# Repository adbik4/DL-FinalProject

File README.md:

# Dokumentacja projektu
## Schemat blokowy

## Schemat ideowy

## Design PCB

## Podgląd 3D

### Blok mikrokontrolera (ATmega328PB)
*Obliczanie wartości pojemności C1 i C2 potrzebnych do zewnętrznego oscylatora MCU:*    

Wybraliśmy CY16BPS ponieważ jego parametry należą do najpopularniejszych do użycia w projektach z tym MCU.    
Oto jego najważniejsze parametry:   
- F_XTAL = 16 MHz
- C_load = 20 pF
- ESR = 50 ohm

Dla uproszczenia obliczeń, niech C1 = C2.    
Korzystając ze wzoru z dokumentacji ATmega,   
**C = 2 * C_L + C_S**  
gdzie     
C_L - Pojemnosć obciążenia kryształu,   
C_S - Pojemność pasożytnicza płytki PCB, niech wynosi 2 pF
    
Dla naszego kryształu C_L wynosi 20 pF    
**Stąd wynika, że C powinno mieć wartość około 42 pF.**

### Diody LED do sygnalizacji
*Obliczanie wartości rezystancji R1, R2 i R3 potrzebnych do uregulowania pracy diód:*     
    
Napięcie zasilania: 3.3V
Kolor diód LED: zielony co oznacza spadek napięcia około 2.2V   
Chcemy ustalić bezpieczny punkt pracy, powiedzmy 10mA    
Z prawa ohma: R = U / I = (3.3 - 2.2) / 10 mA = **110 ohm**

### Rezystancja podciągająca dla linii I2C
Wartość rezystancji podciągającej dla I2C jest wymianą pomiędzy możliwą prędkością wymiany danych a zużyciem energii.     

Zbyt mała wartość może uniemożliwić pinowi układu scalonego z którym się komunikujemy zwarcie linii z masą. Zalezy ona więc od najniższego napięcia jaka może być odczytana przez dany ukł. (U_OL) oraz prądu jaki jest on w stanie wytrzymać (I_OL).     

**R_min = (V_CC - U_OLmax) / I_OL**     

Zbyt duża zaś, przy dużych prędkościach może nie nadążyć z naładowaniem pojemności magistrali (C_m) przed nadejściem kolejnego stanu niskiego. W związku z tym, zależy ona od czasu narastania zboczy.     

**R_max = t_r / (0.8473 * C_m)**     
*Wartość 0.8473 = -ln(0.3) wynika z czasu ładowania pojemności od  30% - 70%*     

Przy naszych małych prędkościach komunikacji oraz z pojedynczym urządzeniem na magistrali, przyjmiemy standardową wartość **4.7kΩ.**

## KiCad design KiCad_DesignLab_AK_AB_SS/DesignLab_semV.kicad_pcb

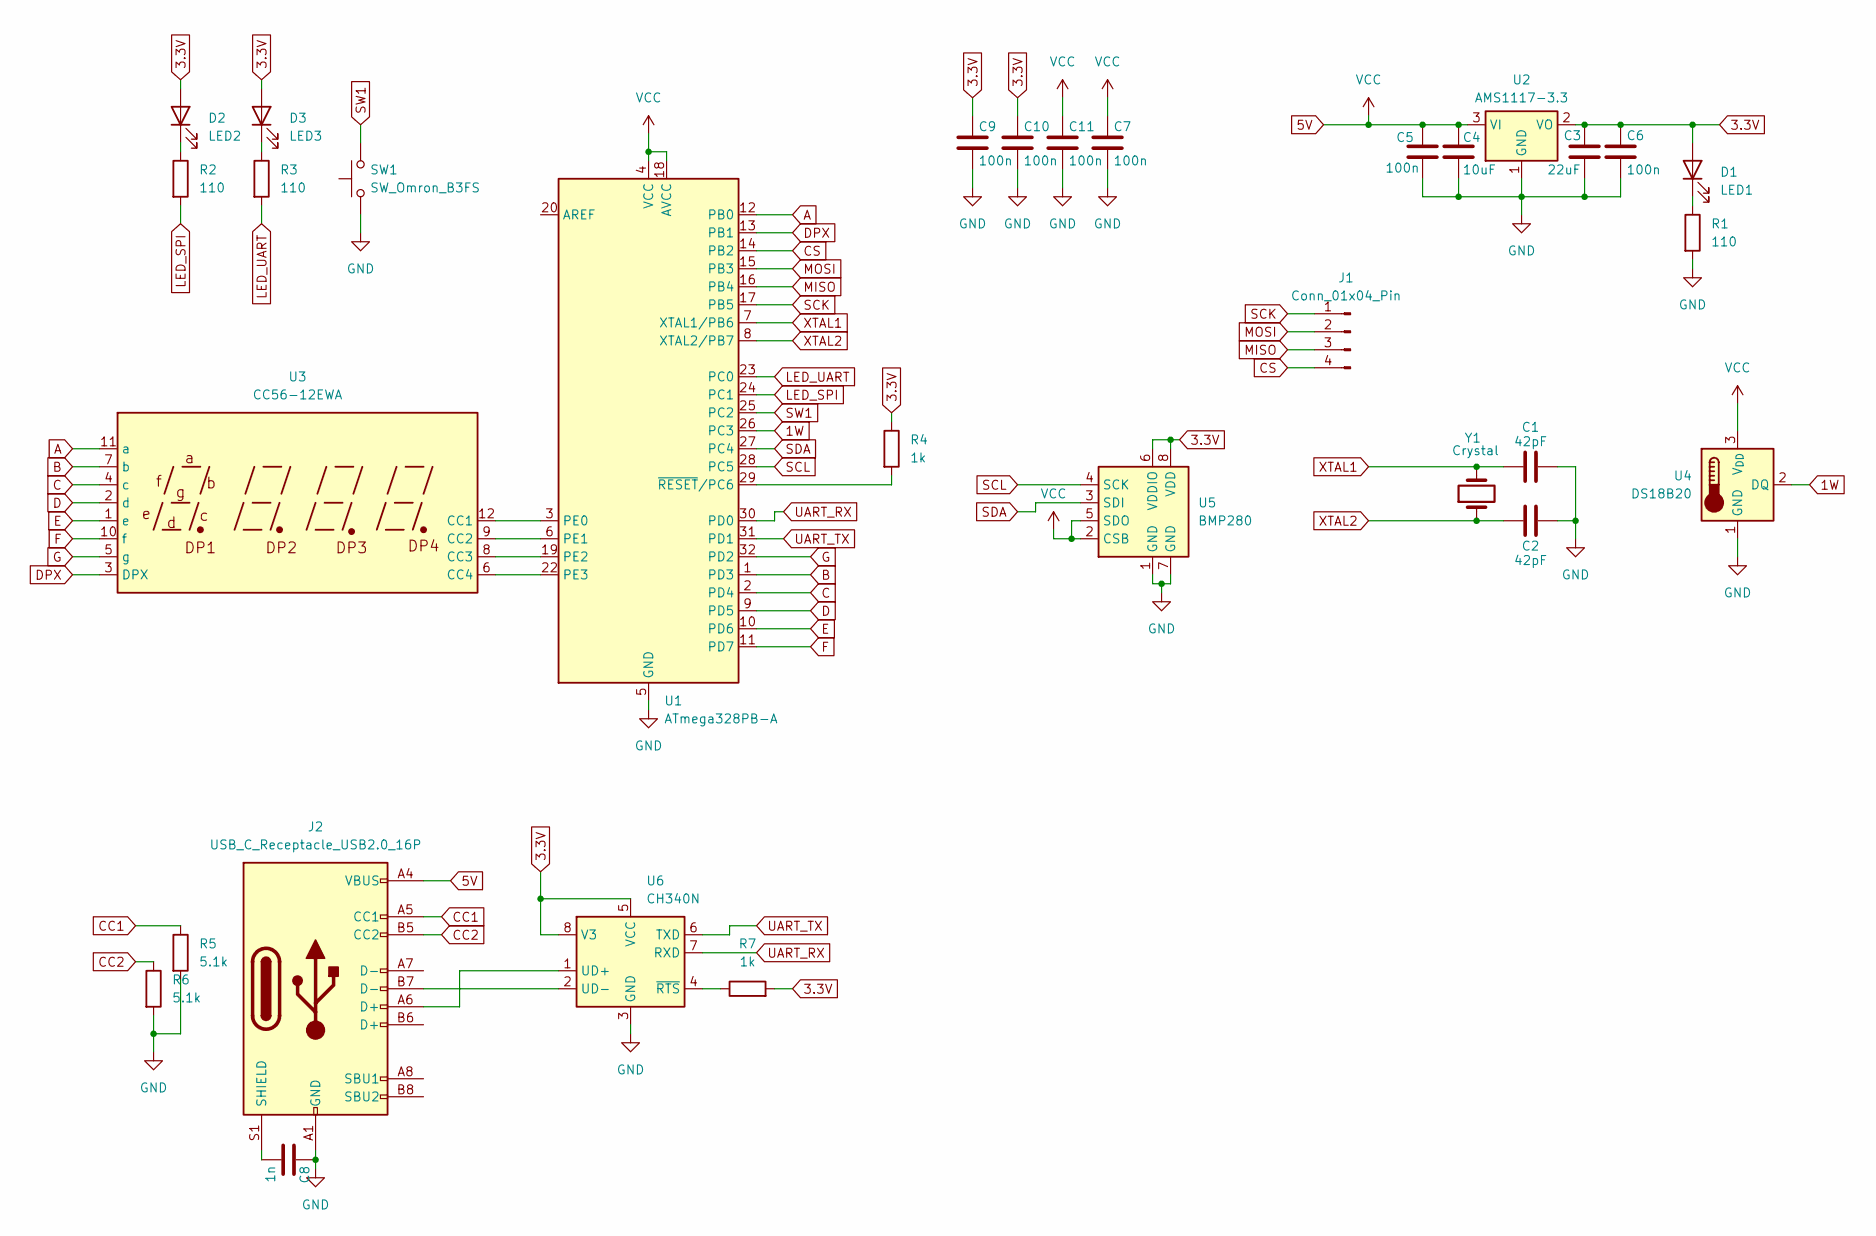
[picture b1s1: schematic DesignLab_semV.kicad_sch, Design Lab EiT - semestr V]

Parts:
C1, C2: 42pF; C_0603_1608Metric
C3: 22uF; C_0603_1608Metric
C4: 10uF; C_0603_1608Metric
C5, C6, C7, C9, C10, C11: 100n; C_0603_1608Metric
C8: 1n; C_0603_1608Metric
D1: LED1; LED_0603_1608Metric
D2: LED2; LED_0603_1608Metric
D3: LED3; LED_0603_1608Metric
J1: Conn_01x04_Pin; PinHeader_1x04_P1.00mm_Vertical
J2: USB_C_Receptacle_USB2.0_16P; USB_C_Receptacle_GCT_USB4085
R1, R2, R3: 110; R_0603_1608Metric
R4, R7: 1k; R_0603_1608Metric
R5, R6: 5.1k; R_0603_1608Metric
SW1: SW_Omron_B3FS; SW_SPST_Omron_B3FS-100xP
U1: ATmega328PB-A; TQFP-32_7x7mm_P0.8mm
U2: AMS1117-3.3; SOT-223-3_TabPin2
U3: CC56-12EWA; CA56-12EWA
U4: DS18B20; TO-92_Inline
U5: BMP280; Bosch_LGA-8_2x2.5mm_P0.65mm_ClockwisePinNumbering
U6: CH340N; JEITA_SOIC-8_3.9x4.9mm_P1.27mm
Y1: Crystal; Crystal_SMD_1210-4Pin_1.2x1.0mm

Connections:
1W: U1.26 (PC3), U4.2 (DQ)
3.3V: C3.1, C6.1, C9.1, C10.1, D1.2 (A), D2.2 (A), D3.2 (A), R4.1, R7.2, U2.2 (VO), U5.6 (VDDIO), U5.8 (VDD), U6.5 (VCC), U6.8 (V3); also elsewhere on the board
5V: C4.1, C5.1, C7.1, C11.1, J2.A4 (VBUS), J2.A9 (VBUS), J2.B4 (VBUS), J2.B9 (VBUS), U1.4 (VCC), U1.18 (AVCC), U2.3 (VI), U4.3 (V_{DD}), U5.2 (CSB), U5.5 (SDO)
A: U1.12 (PB0), U3.11 (a)
B: U1.1 (PD3), U3.7 (b)
C: U1.2 (PD4), U3.4 (c)
CC1: J2.A5 (CC1), R5.1
CC2: J2.B5 (CC2), R6.1
CS: J1.4, U1.14 (PB2)
D: U1.9 (PD5), U3.2 (d)
DPX: U1.13 (PB1), U3.3 (DPX)
E: U1.10 (PD6), U3.1 (e)
F: U1.11 (PD7), U3.10 (f)
G: U1.32 (PD2), U3.5 (g)
GND: C1.2, C2.2, C3.2, C4.2, C5.2, C6.2, C7.2, C8.1, C9.2, C10.2, C11.2, J2.A1 (GND), J2.A12 (GND), J2.B1 (GND), J2.B12 (GND), R1.2, R5.2, R6.2, SW1.1, U1.5 (GND), U1.21 (GND), U2.1 (GND), U4.1 (GND), U5.1 (GND), U5.7 (GND), U6.3 (GND)
LED_SPI: R2.2, U1.24 (PC1)
LED_UART: R3.2, U1.23 (PC0)
MISO: J1.3, U1.16 (PB4)
MOSI: J1.2, U1.15 (PB3)
unnamed: D1.1 (K), R1.1
unnamed: D2.1 (K), R2.1
unnamed: D3.1 (K), R3.1
unnamed: C8.2, J2.S1 (SHIELD)
unnamed: U1.3 (PE0), U3.12 (CC1)
unnamed: U1.6 (PE1), U3.9 (CC2)
unnamed: U1.19 (PE2), U3.8 (CC3)
unnamed: U1.22 (PE3), U3.6 (CC4)
unnamed: R4.2, U1.29 (~RESET/PC6)
unnamed: J2.A6 (D+), U6.1 (UD+)
unnamed: J2.B7 (D-), U6.2 (UD-)
unnamed: R7.1, U6.4 (~RTS)
SCK: J1.1, U1.17 (PB5)
SCL: U1.28 (PC5), U5.4 (SCK); also elsewhere on the board
SDA: U1.27 (PC4), U5.3 (SDI); also elsewhere on the board
SW1: SW1.2, U1.25 (PC2)
UART_RX: U1.30 (PD0), U6.7 (RXD)
UART_TX: U1.31 (PD1), U6.6 (TXD)
XTAL1: C1.1, U1.7 (XTAL1/PB6), Y1.2
XTAL2: C2.1, U1.8 (XTAL2/PB7), Y1.1

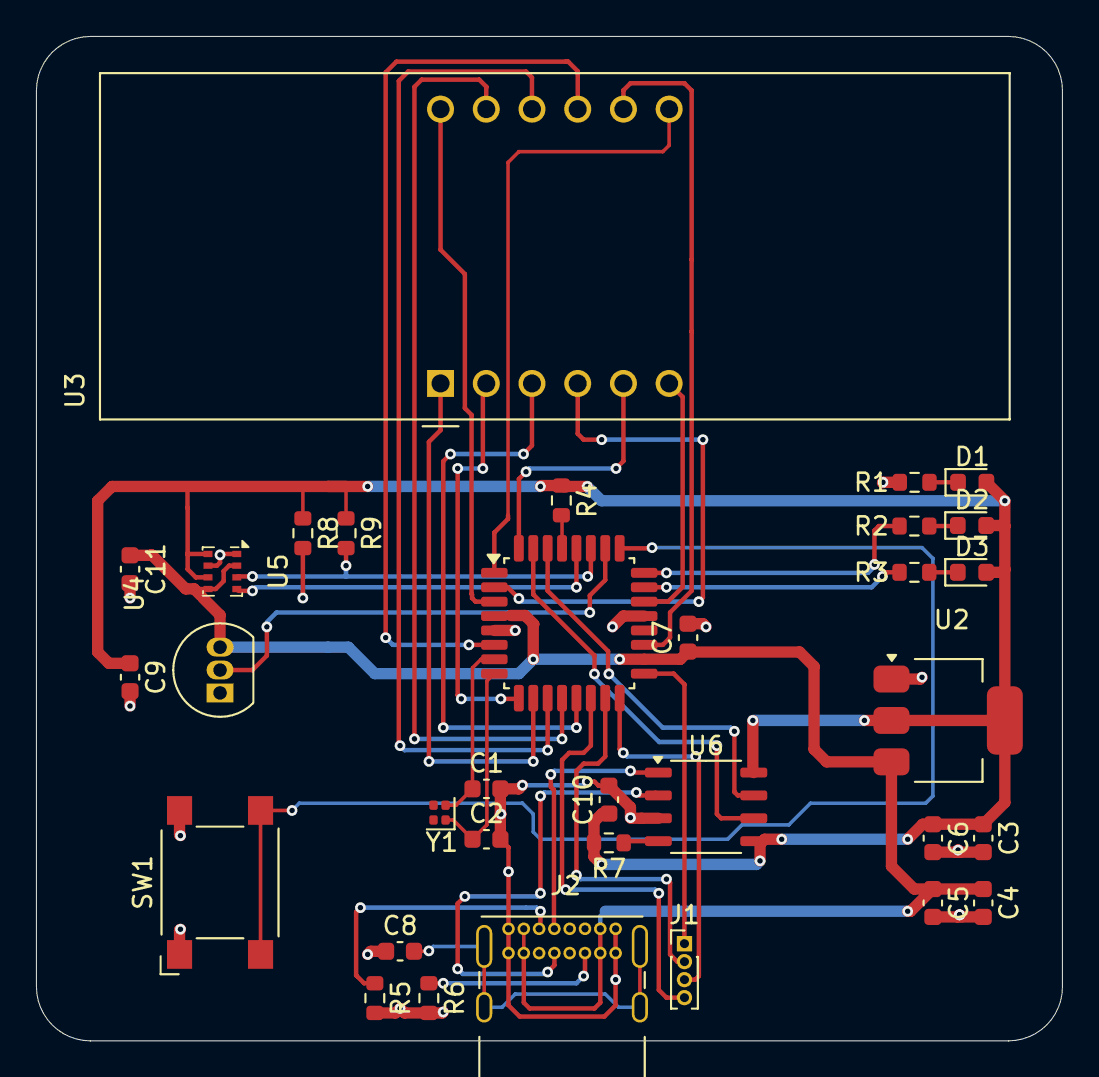
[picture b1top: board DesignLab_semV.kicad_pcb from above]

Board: 2 copper layers, 57.0 x 55.8 mm, 33 parts (0 on the bottom side), 39 nets.

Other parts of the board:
R8, R9: 4.7k; R_0603_1608Metric

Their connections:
3.3V: R8.1, R9.1; also elsewhere on the board
SCL: R8.2; also elsewhere on the board
SDA: R9.2; also elsewhere on the board

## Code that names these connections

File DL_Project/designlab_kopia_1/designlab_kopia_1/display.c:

#include "main.h"
#include "display.h"

#define SEG_PORT_CTRL   PORTE
#define SEG_DDR_CTRL    DDRE
#define SEG_DIGIT1      PE0     // First digit control pin
#define SEG_DIGIT2      PE1     // Second digit control pin
#define SEG_DIGIT3      PE2     // Third digit control pin
#define SEG_DIGIT4      PE3     // Fourth digit control pin

// 7-Segment display segment pins
// Segments are connected to PD2-PD7, PB0-PB1
#define SEG_DDR_DATA1   DDRD    // For segments on Port D
#define SEG_PORT_DATA1  PORTD   // For segments on Port D
#define SEG_DDR_DATA2   DDRB    // For segments on Port B
#define SEG_PORT_DATA2  PORTB   // For segments on Port B

volatile uint8_t seg_digit = 0;    // Current digit being displayed (0-3)
uint8_t seg_values[4] = {0, 0, 0, 0}; // Values to display on each digit


// Bits mapped as: F E D C B G DP A
const uint8_t seven_seg_digits[] = {
	0b00000110,  // 0: A B C D E F
	0b11100111,  // 1: B C
	0b10010010,  // 2: A B D E G
	0b11000010,  // 3: A B C D G
	0b01100011,  // 4: B C F G
	0b01001010,  // 5: A C D F G
	0b00001010,  // 6: A C D E F G
	0b11100110,  // 7: A B C
	0b00000010,  // 8: A B C D E F G
	0b01000010,   // 9: A B C D F G
	
};

void SevenSeg_Init(void) {
	// Configure digit control pins as outputs (active LOW, initially high)
	SEG_DDR_CTRL |= (1 << SEG_DIGIT1) | (1 << SEG_DIGIT2) | (1 << SEG_DIGIT3) | (1 << SEG_DIGIT4);
	SEG_PORT_CTRL |= (1 << SEG_DIGIT1) | (1 << SEG_DIGIT2) | (1 << SEG_DIGIT3) | (1 << SEG_DIGIT4);
	
	// Configure segment pins as outputs (active LOW, initially high)
	// PD2-PD7 for segments
	SEG_DDR_DATA1 |= 0xFC;  // 0b11111100 = bits 2-7
	SEG_PORT_DATA1 |= 0xFC; // All segments off initially
	
	// PB0-PB1 for remaining segments
	SEG_DDR_DATA2 |= 0x03;  // 0b00000011 = bits 0-1
	SEG_PORT_DATA2 |= 0x03; // All segments off initially
	
	
	// Set up Timer0 for display multiplexing
	TCCR0A = (1 << WGM01);              
	TCCR0B = (1 << CS01) | (1 << CS00); 
	OCR0A = 249;                        
	TIMSK0 = (1 << OCIE0A);            
}

void SevenSeg_Update(void) {
	
	SEG_PORT_CTRL |= (1 << SEG_DIGIT1) | (1 << SEG_DIGIT2) | (1 << SEG_DIGIT3) | (1 << SEG_DIGIT4);
	
	
	uint8_t pattern = 0xFF;  
	if (seg_values[seg_digit] < 16) {
		pattern = seven_seg_digits[seg_values[seg_digit]];
	}
	
	// Output segment pattern to Port D (PD2-PD7)
	SEG_PORT_DATA1 &= 0x03;              
	SEG_PORT_DATA1 |= (pattern & 0xFC);  
	
	// Output segment pattern to Port B (PB0-PB1)
	SEG_PORT_DATA2 &= 0xFC;              
	SEG_PORT_DATA2 |= (pattern & 0x03);  
	
	// Select the current digit 
	switch (seg_digit) {
		case 0:
		SEG_PORT_CTRL &= ~(1 << SEG_DIGIT1);
		break;
		case 1:
		SEG_PORT_CTRL &= ~(1 << SEG_DIGIT2);
		break;
		case 2:
		SEG_PORT_CTRL &= ~(1 << SEG_DIGIT3);
		break;
		case 3:
		SEG_PORT_CTRL &= ~(1 << SEG_DIGIT4);
		break;
	}

	seg_digit = (seg_digit + 1) % 4;
}

// Timer0 Compare A interrupt for 7-segment display multiplexing
ISR(TIMER0_COMPA_vect) {
	SevenSeg_Update();
}

void SevenSeg_Show(int num)
{
	
	if (num < 0) num = 0;
	if (num > 9999) num = 9999;
	
	
	seg_values[3] = num % 10;          
	seg_values[2] = (int)(num / 10.0) % 10;   
	seg_values[1] = (int)(num / 100.0) % 10;  
	seg_values[0] = (int)(num / 1000.0) % 10; 
	
}

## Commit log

2025-10-11 added Docs folder
2025-10-11 LDO karta katalogowa
2025-10-12 added the block diagram
2025-10-19 Project structure changes
2025-10-19 Created the KiCad schematic
2025-10-19 Create Codes
2025-11-04 Renamed project structure
2025-11-04 Created MCStudio project
2025-11-04 Fixed project layout
2025-11-04 add seven display
2025-11-05 Updated the schematic & PCB with a 7seg display and SD card
2025-11-11 Routed power lines
2025-11-11 Finished routing the PCB
2025-11-11 Added 3D preview
2025-11-20 Added UART implementation
2025-11-30 removed inc2 and src2
2025-11-30 Updated the schematic with sensors
2025-11-30 Fixed schematic + footprints
2025-11-30 Layout before routing
2025-11-30 sensors code
2025-11-30 Routed the power lines
2025-12-02 Completed PCB v2.0
2025-12-16 Updated the docs with i2c calculations
2025-12-16 Delete DesignLab_AK_AB_SS directory
    podmiana wersji
2025-12-16 Finalna wersja
2025-12-16 PCB layout modifications
2025-12-16 Fixed project tree
2025-12-16 Updated the documentation
2026-01-14 Some DRC fixes
2026-01-14 Updated the PCB screenshot
2026-01-20 Adding app code
2026-01-20 Adding Final Documentation
2026-01-22 Removed old documentation
